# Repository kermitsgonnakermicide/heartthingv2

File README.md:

# Holtex
<p align="center">

>A tiny, wearable ECG monitor!
</p>

# what even is this?
Holtex is an nRF54L15 based holter monitor paired with a MAX30003, a biopotential AFE. It is designed modularly - wherein the MCU module(which just has a xiao nRF54L15 + a MAX17048 i2c fuel gauge) and the ECG module are on completely seperate boards and are joined together by a castellated header.<br>

the ECG and the MCU communicate over SPI(which, in my opinion is far superior to communicating over simple analog) which opens up a whole new realm of possibilities(and complexities).<br>

the device is tiny, just taking up 6x3 cm(can go FAR smaller) and is connected to the body via this awesome [electrode belt](https://store.upsidedownlabs.tech/product/heart-bioamp-band/)<br>

in terms of battery - i'm just using the cheapest thing on hand and it should(in theory) last at least a day, thanks to [ttf's super optimized firmware](https://github.com/TTF-fog/ArrythmiX)<br>

# why??
i ~~was sold into slavery by a chinese warlord and then ttf forced me to make this~~ requested by my good friend [ttf](https://github.com/TTF-fog) to help him redesign the PCB for their project + test out/evaluate the nRF54 as a viable option - this is also why i'm using their firmware available [here](https://github.com/TTF-fog/ArrythmiX).<br>
i'll be answering some frequently asked questions below<br>
**Q - why xiao?**<br>
because they're tiny and epic, and also because I couldnt figure out how to route antennas and no nRF54 modules were very well documented so i left them <br>
**Q- why max30003???**<br>
only because SPI - also because of bad experiences with the ad8232 <br>

# how can YOU assemble this?
1 - use the BOMs, CPLs and gerbers given to print out all of these PCBs and get them both assembled(you can hold on the xiao and solder it yourself)

2 - print both parts of the case(i'm going to try TPU and see how it goes)

3 - place the PCBs in the case and screw the top to the bottom of the case 

4 - feed the electrode belt through the clips 

5 - place the electrode belt right in the center of your torso

6 - connect via Rerun and visualize data!!

# images
<details>
<summary>PCB images</summary>

>ECG PCB

>MCU PCB

</details>

<details>
<summary>Schematic images</summary>

>ECG Schematic

>MCU Schematic

</details>

<details>
<summary>3D images</summary>

>ECG 3D image

>MCU 3D image

</details>

<details>
<summary>CAD/Renders</summary>

>whole thing with case from the front

>fun animation!!

</details>

# Zine

# BOM
Name | Link | QTY | Unit Price | Total Price | Running Total | Notes
--- | --- | ---: | ---: | ---: | ---: | ---
500 mAh LiPo battery | https://robu.in/product/500mah-pcm-protected-micro-li-po-battery/ | 1 | 2.73 | 2.73 | 2.73 |
MCU PCB | Seeed Fusion | 1 | 73.00 | 73.00 | 75.73 | refer to PCB BOM
ECG PCB | JLCPCB | 1 | 57.00 | 57.00 | 132.73 | refer to PCB BOM
M2.5 Screws (10 mm) | https://onlyscrews.in/products/m2-5-x-10mm-hex-allen-socket-head-high-tensile12-9-black-oxide-screw-dia-2-5mm-length-10mm | 15 | 0.07 | 1.05 | 133.78 |
| | | | |  |
TOTAL | | | | 133.78 | |

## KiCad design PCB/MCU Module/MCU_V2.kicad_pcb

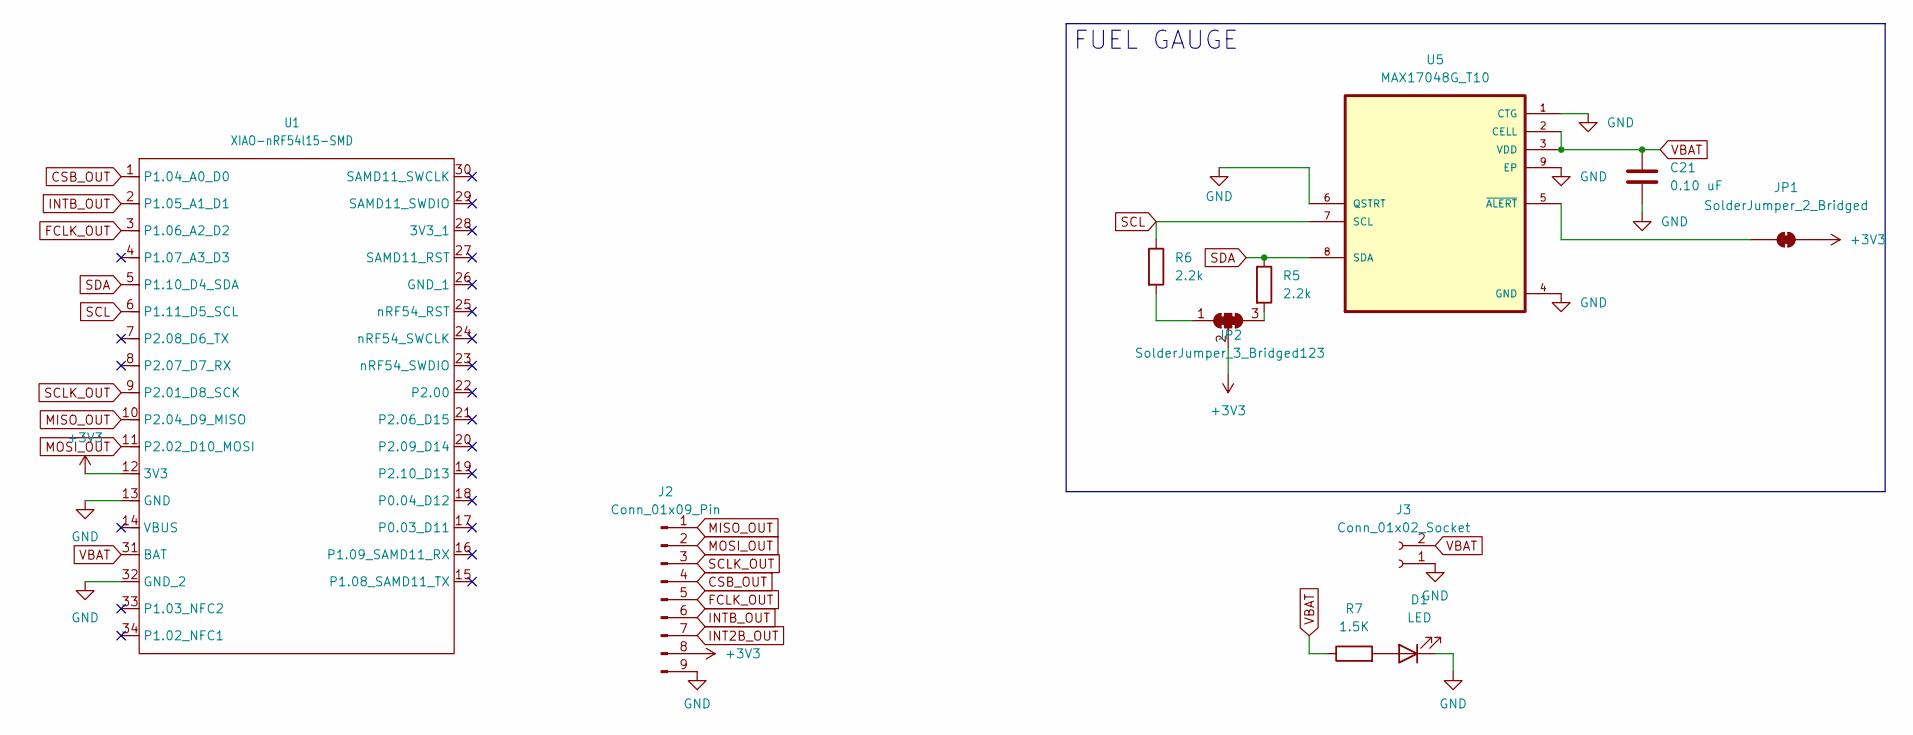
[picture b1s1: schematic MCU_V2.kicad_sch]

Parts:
C21: 0.10 uF; C_0201_0603Metric_Pad0.64x0.40mm_HandSolder
D1: LED; LED_1206_3216Metric
J2: Conn_01x09_Pin; PinSocket_1x09_P2.54mm_Vertical
J3: Conn_01x02_Socket; PinSocket_1x02_P2.54mm_Vertical
JP1: SolderJumper_2_Bridged; SolderJumper-2_P1.3mm_Bridged2Bar_Pad1.0x1.5mm
JP2: SolderJumper_3_Bridged123; SolderJumper-3_P1.3mm_Bridged123_RoundedPad1.0x1.5mm
R5, R6: 2.2k; R_0603_1608Metric
R7: 1.5K; R_0603_1608Metric
U1: XIAO-nRF54l15-SMD
U5: MAX17048G_T10; SON50P200X200X80-9N

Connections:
+3V3: J2.8, JP1.2 (B), JP2.2 (C), U1.12 (3V3)
CSB_OUT: J2.4, U1.1 (P1.04_A0_D0)
FCLK_OUT: J2.5, U1.3 (P1.06_A2_D2)
GND: C21.2, D1.1 (K), J2.9, J3.1, U1.13 (GND), U1.32 (GND_2), U5.1 (CTG), U5.4 (GND), U5.6 (QSTRT), U5.9 (EP)
INT2B_OUT: J2.7
INTB_OUT: J2.6, U1.2 (P1.05_A1_D1)
MISO_OUT: J2.1, U1.10 (P2.04_D9_MISO)
MOSI_OUT: J2.2, U1.11 (P2.02_D10_MOSI)
unnamed: D1.2 (A), R7.2
unnamed: JP1.1 (A), U5.5 (~ALERT)
unnamed: JP2.1 (A), R6.2
unnamed: JP2.3 (B), R5.2
SCL: R6.1, U1.6 (P1.11_D5_SCL), U5.7 (SCL)
SCLK_OUT: J2.3, U1.9 (P2.01_D8_SCK)
SDA: R5.1, U1.5 (P1.10_D4_SDA), U5.8 (SDA)
VBAT: C21.1, J3.2, R7.1, U1.31 (BAT), U5.2 (CELL), U5.3 (VDD)

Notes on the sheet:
FUEL GAUGE

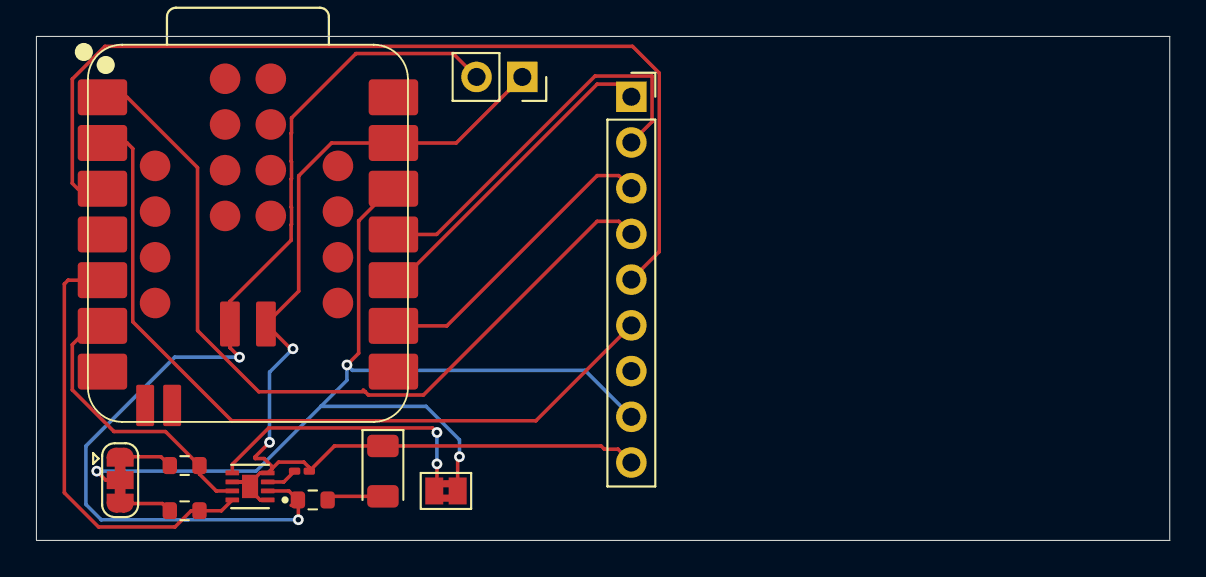
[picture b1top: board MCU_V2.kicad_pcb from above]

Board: 2 copper layers, 63.0 x 28.0 mm, 11 parts (0 on the bottom side), 15 nets.

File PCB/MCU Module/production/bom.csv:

Designator,Footprint,Quantity,Value,LCSC Part #
C21,0201,1,0.10 uF,
D1,1206,1,LED,
J2,PinSocket_1x09_P2.54mm_Vertical,1,Conn_01x09_Pin,
J3,PinSocket_1x02_P2.54mm_Vertical,1,Conn_01x02_Socket,
"R5, R6",0603,2,2.2k,
R7,0603,1,1.5K,
U1,XIAO-nRF54l15-SMD,1,XIAO-nRF54l15-SMD,
U5,SON50P200X200X80-9N,1,MAX17048G_T10,

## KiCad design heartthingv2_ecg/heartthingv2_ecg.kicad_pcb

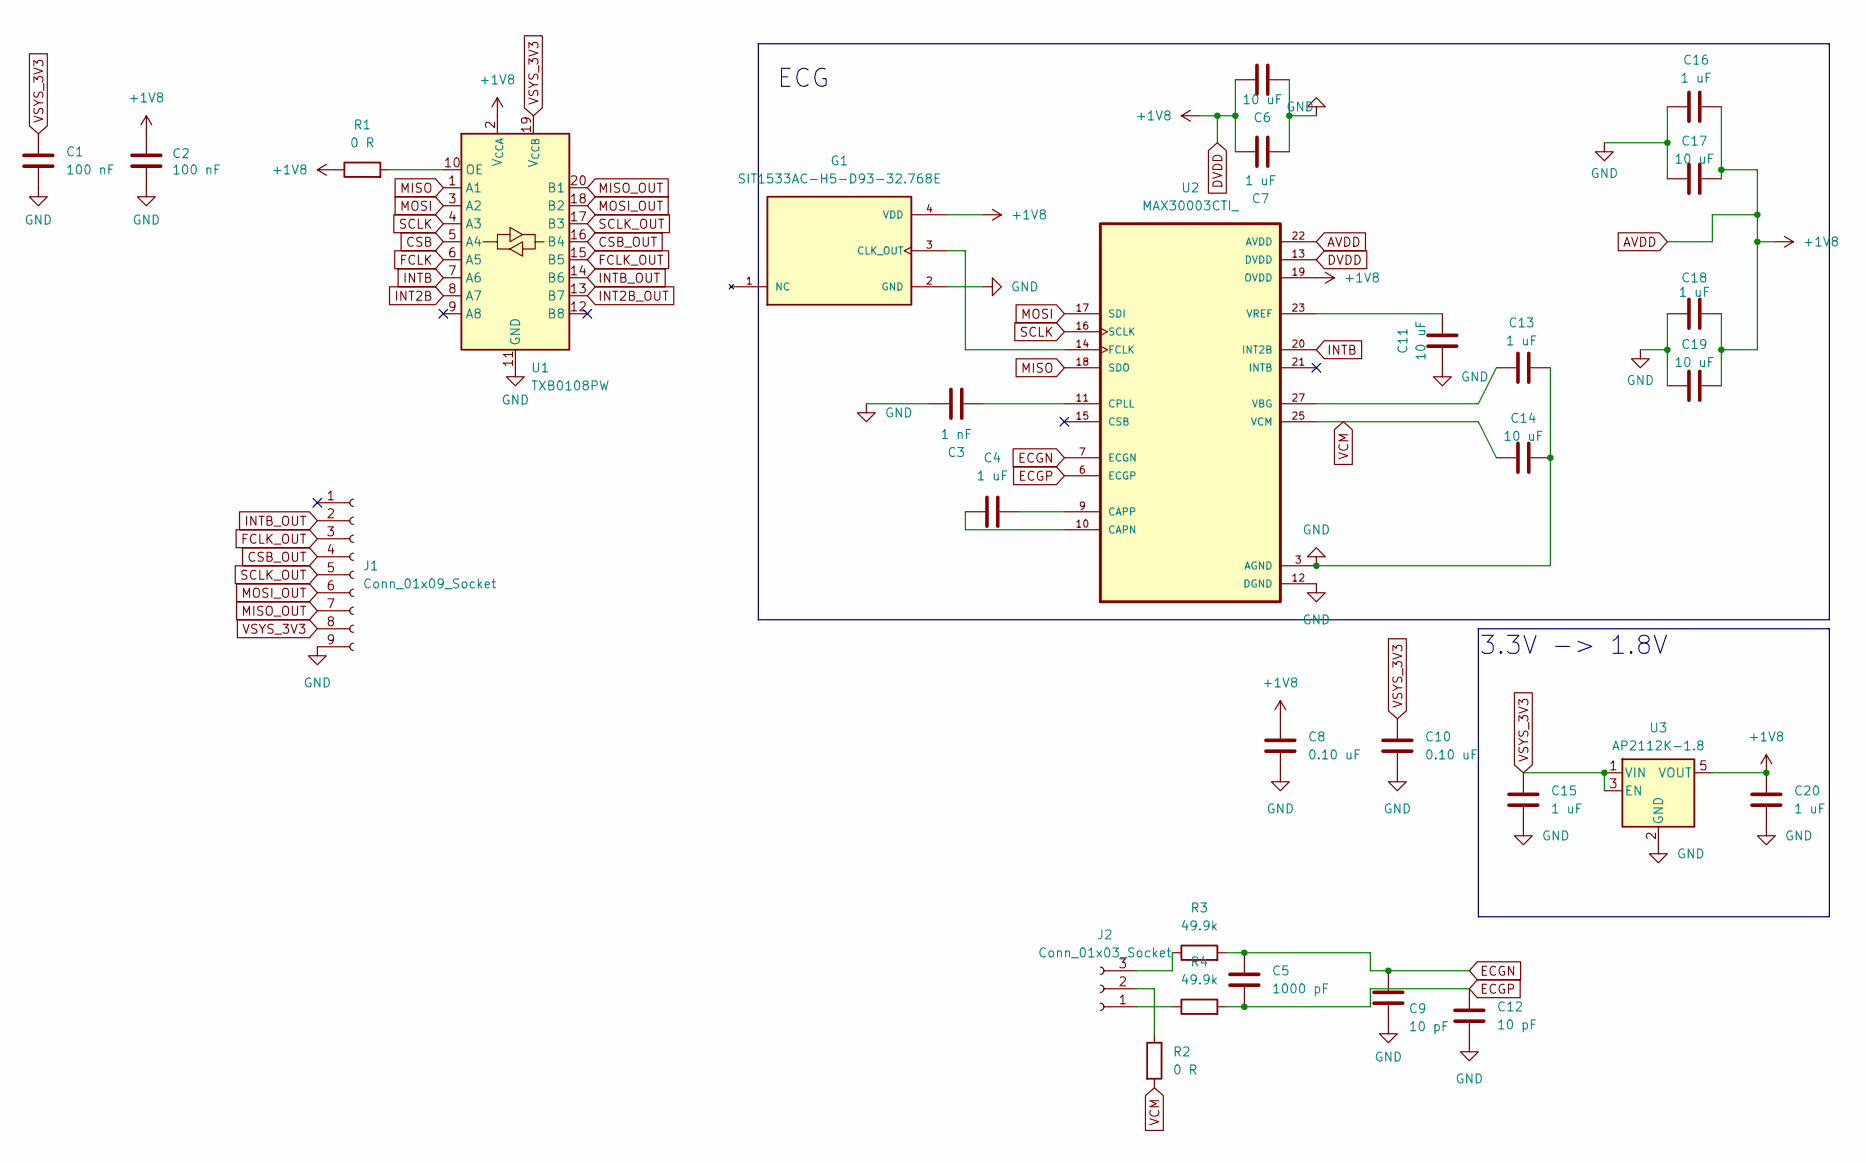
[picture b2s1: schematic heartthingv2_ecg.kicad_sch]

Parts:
C1, C2: 100 nF; C_0603_1608Metric
C3: 1 nF; C_0402_1005Metric
C4, C7, C13, C15, C16, C18, C20: 1 uF; C_0603_1608Metric
C5: 1000 pF; C_0402_1005Metric
C6, C11, C14, C17, C19: 10 uF; C_0805_2012Metric
C8: 0.10 uF; C_0603_1608Metric
C9, C12: 10 pF; C_0402_1005Metric
C10: 0.10 uF; C_0402_1005Metric
G1: SIT1533AC-H5-D93-32.768E; OSC_SIT1533AC-H5-D93-32.768E; PARTREV 1.4
J1: Conn_01x09_Socket; PinSocket_1x09_P2.54mm_Vertical
J2: Conn_01x03_Socket; PinSocket_1x03_P2.54mm_Vertical
R1, R2: 0 R; R_0805_2012Metric
R3, R4: 49.9k; R_0805_2012Metric
U1: TXB0108PW; TSSOP-20_4.4x6.5mm_P0.65mm
U2: MAX30003CTI_; QFN50P500X500X80-29N
U3: AP2112K-1.8; SOT-23-5

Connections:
AVDD: C2.1, C6.2, C7.2, C8.1, C16.2, C17.2, C18.2, C19.2, C20.1, G1.4 (VDD), R1.1, U1.2 (V_{CCA}), U2.13 (DVDD), U2.19 (OVDD), U2.22 (AVDD), U3.5 (VOUT)
CSB: U1.5 (A4)
CSB_OUT: J1.4, U1.16 (B4)
ECGN: C5.1, C9.1, R3.2, U2.7 (ECGN)
ECGP: C5.2, C12.1, R4.2, U2.6 (ECGP)
FCLK: U1.6 (A5)
FCLK_OUT: J1.3, U1.15 (B5)
GND: C1.2, C2.2, C3.2, C6.1, C7.1, C8.2, C9.2, C10.2, C11.1, C12.2, C13.2, C14.2, C15.2, C16.1, C17.1, C18.1, C19.1, C20.2, G1.2 (GND), J1.9, U1.11 (GND), U2.3 (AGND), U2.8 (AGND), U2.12 (DGND), U2.28 (AGND), U2.29 (AGND), U3.2 (GND)
INT2B: U1.8 (A7)
INT2B_OUT: U1.13 (B7)
INTB: U1.7 (A6), U2.20 (INT2B)
INTB_OUT: J1.2, U1.14 (B6)
MISO: U1.1 (A1), U2.18 (SDO)
MISO_OUT: J1.7, U1.20 (B1)
MOSI: U1.3 (A2), U2.17 (SDI)
MOSI_OUT: J1.6, U1.18 (B2)
unnamed: G1.3 (CLK_OUT), U2.14 (FCLK)
unnamed: J2.1, R4.1
unnamed: J2.2, R2.1
unnamed: J2.3, R3.1
unnamed: R1.2, U1.10 (OE)
unnamed: C4.1, U2.10 (CAPN)
unnamed: C4.2, U2.9 (CAPP)
unnamed: C3.1, U2.11 (CPLL)
unnamed: C13.1, U2.27 (VBG)
unnamed: C11.2, U2.23 (VREF)
SCLK: U1.4 (A3), U2.16 (SCLK)
SCLK_OUT: J1.5, U1.17 (B3)
VCM: C14.1, R2.2, U2.25 (VCM)
VSYS_3V3: C1.1, C10.1, C15.1, J1.8, U1.19 (V_{CCB}), U3.1 (VIN), U3.3 (EN)

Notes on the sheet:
3.3V -> 1.8V
ECG

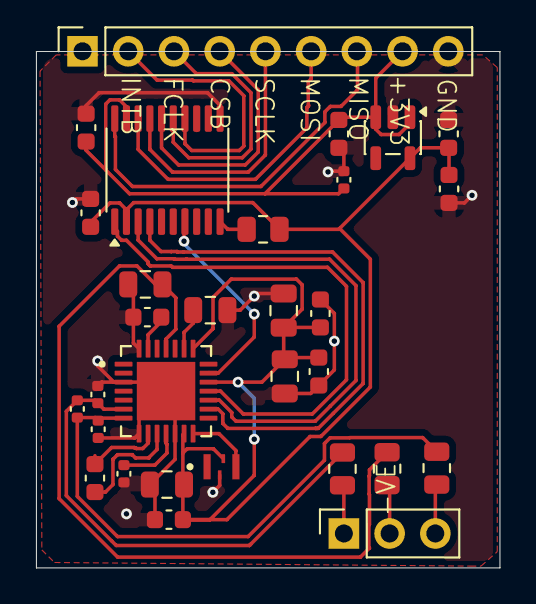
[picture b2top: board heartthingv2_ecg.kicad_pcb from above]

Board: 2 copper layers, 25.8 x 28.7 mm, 30 parts (0 on the bottom side), 26 nets.

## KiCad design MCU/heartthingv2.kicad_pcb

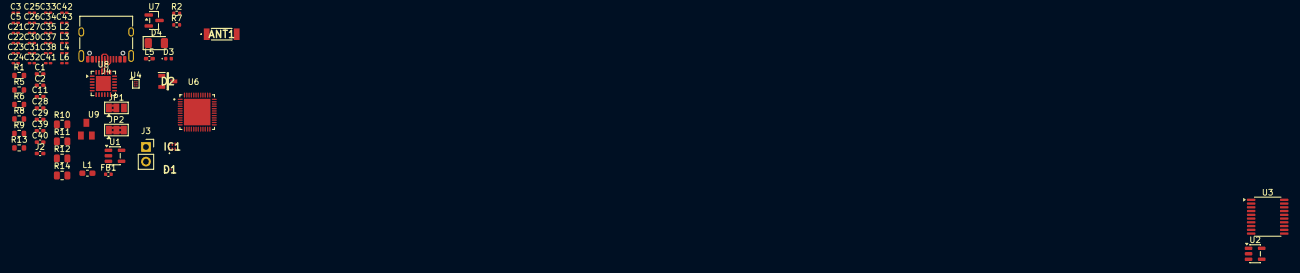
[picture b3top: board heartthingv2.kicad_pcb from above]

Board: 2 copper layers, 65 parts (0 on the bottom side), 38 nets.

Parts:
ANT1: KH5220-A36; KH5220A36
C1, C2, C11: 4.7 uF; C_0402_1005Metric_Pad0.74x0.62mm_HandSolder
C3, C5, C23, C24, C25, C26, C35, C38, C41, C42: 100 nF; C_0201_0603Metric_Pad0.64x0.40mm_HandSolder
C21: 0.10 uF; C_0201_0603Metric_Pad0.64x0.40mm_HandSolder
C22: 3.9 pF; C_0201_0603Metric_Pad0.64x0.40mm_HandSolder
C27, C37: 10 uF; C_0201_0603Metric_Pad0.64x0.40mm_HandSolder
C28, C29: 2.2 uF; C_0402_1005Metric_Pad0.74x0.62mm_HandSolder
C30: 10 nF; C_0201_0603Metric_Pad0.64x0.40mm_HandSolder
C31: 2.2 nF; C_0201_0603Metric_Pad0.64x0.40mm_HandSolder
C32: 1.5 pF; C_0201_0603Metric_Pad0.64x0.40mm_HandSolder
C33: 2.0 pF; C_0201_0603Metric_Pad0.64x0.40mm_HandSolder
C34: 0.3 pF; C_0201_0603Metric_Pad0.64x0.40mm_HandSolder
C39, C40: 1.0 uF; C_0402_1005Metric_Pad0.74x0.62mm_HandSolder
C43: 1 pF; C_0201_0603Metric_Pad0.64x0.40mm_HandSolder
D1: DF2B7ASL,L3F; DF2B7ASLL3F
D2: DMG2305UX-13; SOT96P240X120-3N
D3: PSBD2FD40V1H; D_0402_1005Metric
D4: LED; LED_1206_3216Metric
FB1: 120; C_0402_1005Metric
IC1: UM3301DA
J2: Conn_01x09_Pin; C_0402_1005Metric_Pad0.74x0.62mm_HandSolder
J3: Conn_01x02_Socket; PinSocket_1x02_P2.54mm_Vertical
J4: USB_C_Receptacle_USB2.0_16P; USB_C_Receptacle_XKB_U262-16XN-4BVC11
JP1: SolderJumper_2_Bridged; SolderJumper-3_P1.3mm_Bridged2Bar12_Pad1.0x1.5mm
JP2: SolderJumper_3_Bridged123; SolderJumper-3_P1.3mm_Bridged2Bar123_Pad1.0x1.5mm
L1: 4.7 uH; L_0603_1608Metric_Pad1.05x0.95mm_HandSolder
L2: 2.7 nH; L_0201_0603Metric_Pad0.64x0.40mm_HandSolder
L3, L4: 3.5 nH; L_0201_0603Metric_Pad0.64x0.40mm_HandSolder
L5: 1 uH; L_0402_1005Metric_Pad0.77x0.64mm_HandSolder
L6: 6.8 nH; L_0201_0603Metric_Pad0.64x0.40mm_HandSolder
R1: 2k; R_0603_1608Metric
R2: 470; R_0402_1005Metric
R5, R6: 2.2k; R_0603_1608Metric
R7: 1k; R_0402_1005Metric
R8, R9: 5.1k; R_0603_1608Metric
R10: 249k; R_0805_2012Metric
R11, R12: 100K; R_0805_2012Metric
R13: 10K; R_0603_1608Metric
R14: 100k; R_0805_2012Metric
U1: MCP73831-2-OT; SOT-23-5
U2: AP2112K-1.8; SOT-23-5
U3: TXB0108PW; TSSOP-20_4.4x6.5mm_P0.65mm
U4: TPS628438DRL; Texas_DSBGA-6_0.757x1.01mm_Layout2x3_P0.35mm
U6: NRF54L15-QFAA-R; QFN40P600X600X90-49N
U7: MCP1700x-120xxTT; SOT-23
U8: ATSAMD11D14A-M; QFN-24-1EP_4x4mm_P0.5mm_EP2.6x2.6mm
U9: AO3400; SOT23

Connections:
ANT: C34.1, L4.2, L6.1
ANT_PIN: L2.1, U6.31 (ANT)
DCC: L1.1, U6.46 (DCC)
DEBUG_D+: J4.A6 (D+), J4.B6 (D+), U8.22 (PA25)
DEBUG_D-: J4.A7 (D-), J4.B7 (D-), U8.21 (PA24)
DECA: C29.1, C30.1, C31.1, FB1.1, U6.33 (DECRF), U6.43 (DECA)
DECD: C28.1, FB1.2, L1.2, U6.45 (DECD)
DVDD: U2.5 (VOUT), U3.2 (V_{CCA})
GND: C1.2, C2.1, C3.2, C5.2, C11.2, C21.2, C22.2, C23.2, C24.2, C25.2, C26.2, C27.2, C28.2, C29.2, C30.2, C31.2, C33.2, C34.2, C35.2, C37.2, C38.2, C39.2, C40.2, C41.2, C42.2, C43.2, D1.1 (A1), IC1.2 (GND), J3.1, J4.A1 (GND), J4.A12 (GND), J4.B1 (GND), J4.B12 (GND), J4.SH (SHIELD), JP1.1 (A), R1.2, R8.2, R9.2, R10.2, R11.2, R13.2, R14.2, U1.5 (PROG), U2.2 (GND), U3.11 (GND), U6.44 (VSS), U6.49 (VSS), U7.1 (GND), U8.23 (GND), U9.2
MISO_OUT: J2.1, U3.20 (B1), U6.13 (P2.02)
MOSI_OUT: J2.2, U3.18 (B2), U6.15 (P2.04)
unnamed: ANT1.1 (INPUT_1), C43.1, L6.2
unnamed: C22.1, R7.1
unnamed: C32.1, L2.2, L3.1
unnamed: C33.1, L3.2, L4.1
unnamed: D4.1 (K), R2.1
unnamed: IC1.4 (B), U8.1 (PA02)
unnamed: J4.A5 (CC1), R8.1
unnamed: J4.B5 (CC2), R9.1
unnamed: JP2.1 (A), R6.2
unnamed: JP2.3 (B), R5.2
unnamed: R2.2, U1.1 (STAT)
unnamed: R1.1, U1.2 (V_{SS})
unnamed: R14.1, U8.3 (PA04), U9.1
P1.08/SAMD11_TX: U6.9 (P1.08/CLK16M/EXTREF), U8.7 (PA08/XIN)
P1.09/SAMD11_RX: U6.37 (P1.09/ASO(2)/RADIO(0)), U8.4 (PA05)
SAMD11_3V3: C40.1, C42.1, IC1.5 (OE), IC1.6 (VCCB), R12.1, R13.1, U7.2 (VO), U8.24 (VDD)
SAMD11_RESET: C41.1, R12.2, U8.18 (PA28/~RST)
SCLK_OUT: U3.17 (B3), U6.12 (P2.01)
USB_5V_IN: C1.1, C35.1, C38.1, C39.1, D1.2 (A2), D2.1 (G), D3.2 (A), D4.2 (A), J4.A4 (VBUS), J4.A9 (VBUS), J4.B4 (VBUS), J4.B9 (VBUS), R11.1, U1.4 (V_{DD}), U7.3 (VI)
VBAT: C2.2, C21.1, D2.3 (D), J3.2, U1.3 (V_{BAT})
VBUS: C11.1, D2.2 (S), D3.1 (K)
VCC: JP1.2 (B), JP2.2 (C), U2.1 (VIN), U2.3 (EN), U3.19 (V_{CCB})
VDD: C5.1, C23.1, C24.1, C25.1, C26.1, C27.1, C37.1, IC1.3 (A), L5.2, U6.10 (VDD), U6.22 (VDD), U6.36 (VDD), U6.47 (VDD), U6.48 (VDD)
VSS_PA: C32.2, U6.32 (VSS_PA)
nRF54_RESET: R7.2, U6.30 (~RESET), U9.3
nRF54_SWCLK: U6.26 (SWDCLK), U8.2 (PA03)
nRF54_SWDIO: IC1.1 (VCCA), U6.25 (SWDIO)

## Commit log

2026-05-23 WEAW
2026-05-24 no diddy
2026-06-09 jignesh
2026-06-09 six seven
2026-06-09 idk amn
2026-06-10 do 3D stuff
2026-06-10 reorganization
2026-06-10 delte
2026-06-11 jogeshwari
2026-06-11 final done ok thankyoubaibai
2026-06-11 Revise BOM.csv for improved formatting and details
    Updated item names and prices for clarity and consistency.
